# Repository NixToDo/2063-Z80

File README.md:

# Retro Z80 CPU Board

This project is a small changed copy of the great design from John Winans. I have added a J3A1 connector to get the IORQ_50, IORQ_60 and SIO_IEO from the PCB.

This project was designed to run CP/M 2.2 from an SD card.  It should be an attainable goal for anyone that can solder through-hole parts to assemble it. Note that J10 is an optional header that allows a Sparkfun SD card breakout board [DEV-13743](https://www.digikey.com/en/products/detail/sparkfun-electronics/DEV-13743/5881845) to used instead of soldering on the surface-mount SD socket part.

## Where to get Boards & Software

* You can order boards from any prototype PCB vendor.  For example, I show how you can order these boards from [JLCPCB](https://jlcpcb.com/) or [OSHPark](https://oshpark.com/) by uploading the gerber files found in the releases of this and the flash programmer projects as shown in this [Z80 Retro! - How To Order PC Boards](https://youtu.be/AUg_sbPnzn0) video on YouTube.
  - Gerber files for the CPU board: [2063-Z80-v3](https://github.com/johnwinans/2063-Z80/releases/download/v3/2063-Z80-gerbers.zip)
  - Gerber files for the FLASH programmer: [2065-Z80-programmer-v2](https://github.com/johnwinans/2065-Z80-programmer/releases/download/v2.0/2065-Z80-programmer-gerbers.zip) (This is used with a Raspberry PI to program the FLASH chip on the CPU board.)

* Software for this project can be found in my [2063-Z80-cpm](https://github.com/johnwinans/2063-Z80-cpm) repo.

* Note that the [FLASH programmer](https://github.com/johnwinans/2065-Z80-programmer) has been designed to work with a Raspberry PI in the event that you don't already own such programmer.  This companion programmer PCB should cost about $2 more when it is ordered at the same time as the CPU board from JLCPCB or other similar proto-board shops as shown in the [Z80 Retro! - How To Order PC Boards](https://youtu.be/AUg_sbPnzn0) video on YouTube.

## Links to Related Material

* A youtube playlist discussing this project and how to build your own can be found in [John's Basement](https://www.youtube.com/watch?v=oekucjDcNbA&list=PL3by7evD3F51Cf9QnsAEdgSQ4cz7HQZX5)
* A PDF version of the schematic can be found [here](2063-Z80.pdf).
* Here is the as-built [BOM](2063-Z80.md) with links to the datasheets for all the parts.
* Here is another [BOM](2063-Z80-sockets.md) with links to sockets for the chips.
* To configure a new PI for use with this programmer board as well as to develop Z80 code 
for the Z80 Retro board, see this [PI Setup Guide](https://github.com/johnwinans/raspberry-pi-install)
* More software for this project will be added as it evolves.

## Links to Related Datasheets Seen On YouTube

* [Z80 Datasheet PS0178](https://www.zilog.com/docs/z80/ps0178.pdf) with detailed timing diagrams.
* [Z80 User Manual UM0080](http://www.zilog.com/docs/z80/um0080.pdf) with detailed descriptions of each instruction.
* [Z80 CPU Peripherals User Manual UM0081](http://www.zilog.com/docs/z80/um0081.pdf) discusses the CTC and SIO.
* [Z80 Family Product Specifications Handbook - 1984](http://www.bitsavers.org/components/zilog/z80/Z80_Family_Product_Specifications_Handbook_Feb84.pdf) has nicer pictures of the SIO registers.
* [Wikipedia UART Article](https://en.wikipedia.org/wiki/Universal_asynchronous_receiver-transmitter)
* [AY-3-1015D UART Datasheet](https://rocelec.widen.net/view/pdf/bvesdj0cqf/GSIIS01845-1.pdf) (Has a discussion of the 16X bit-rate clock with diagrams etc. applicable to all UARTs.)

## Serial Port Cable Parts

* [How to make IDC cables](https://youtu.be/gZ420Z-8HuU) for the serial ports.
* [IDC 2x5 connectors](https://www.amazon.com/gp/product/B07S1NFG4S)
* [IDC D-SUB 9-pin connectors (Digikey)](https://www.digikey.com/en/products/detail/assmann-wsw-components/A-DSF-09LPIII-Z/924263)
* [IDC D-SUB 9-pin connectors (Amazon)](https://www.amazon.com/Uxcell-a15030600ux0494-Female-Connector-Ribbon/dp/B00YM41NTW)

## Parallel Port Cable Parts

* [IDC 2x13 connectors](https://www.amazon.com/gp/product/B07RXK96GV)
* [IDC D-SUB 25-pin connectors (Digikey)](https://www.digikey.com/en/products/detail/amphenol-icc-commercial-products/L17DBFRA25S/1972210)
* [IDC D-SUB 25-pin connectors (Amazon)](https://www.amazon.com/Fielect-Female-Adapter-Connector-Ribbon/dp/B082GMDNTS)

## Ribbon Cable

* [40-conductor (Amazon)](https://www.amazon.com/Eowpower-40Pin-40Way-Rainbow-Ribbon/dp/B079KQ6K3Y) - peel off a
 26-pin strip and a 10-pin strip to make one parallel and one serial cable (cut the 10-pin strip in half length-wise to make two serial cables.

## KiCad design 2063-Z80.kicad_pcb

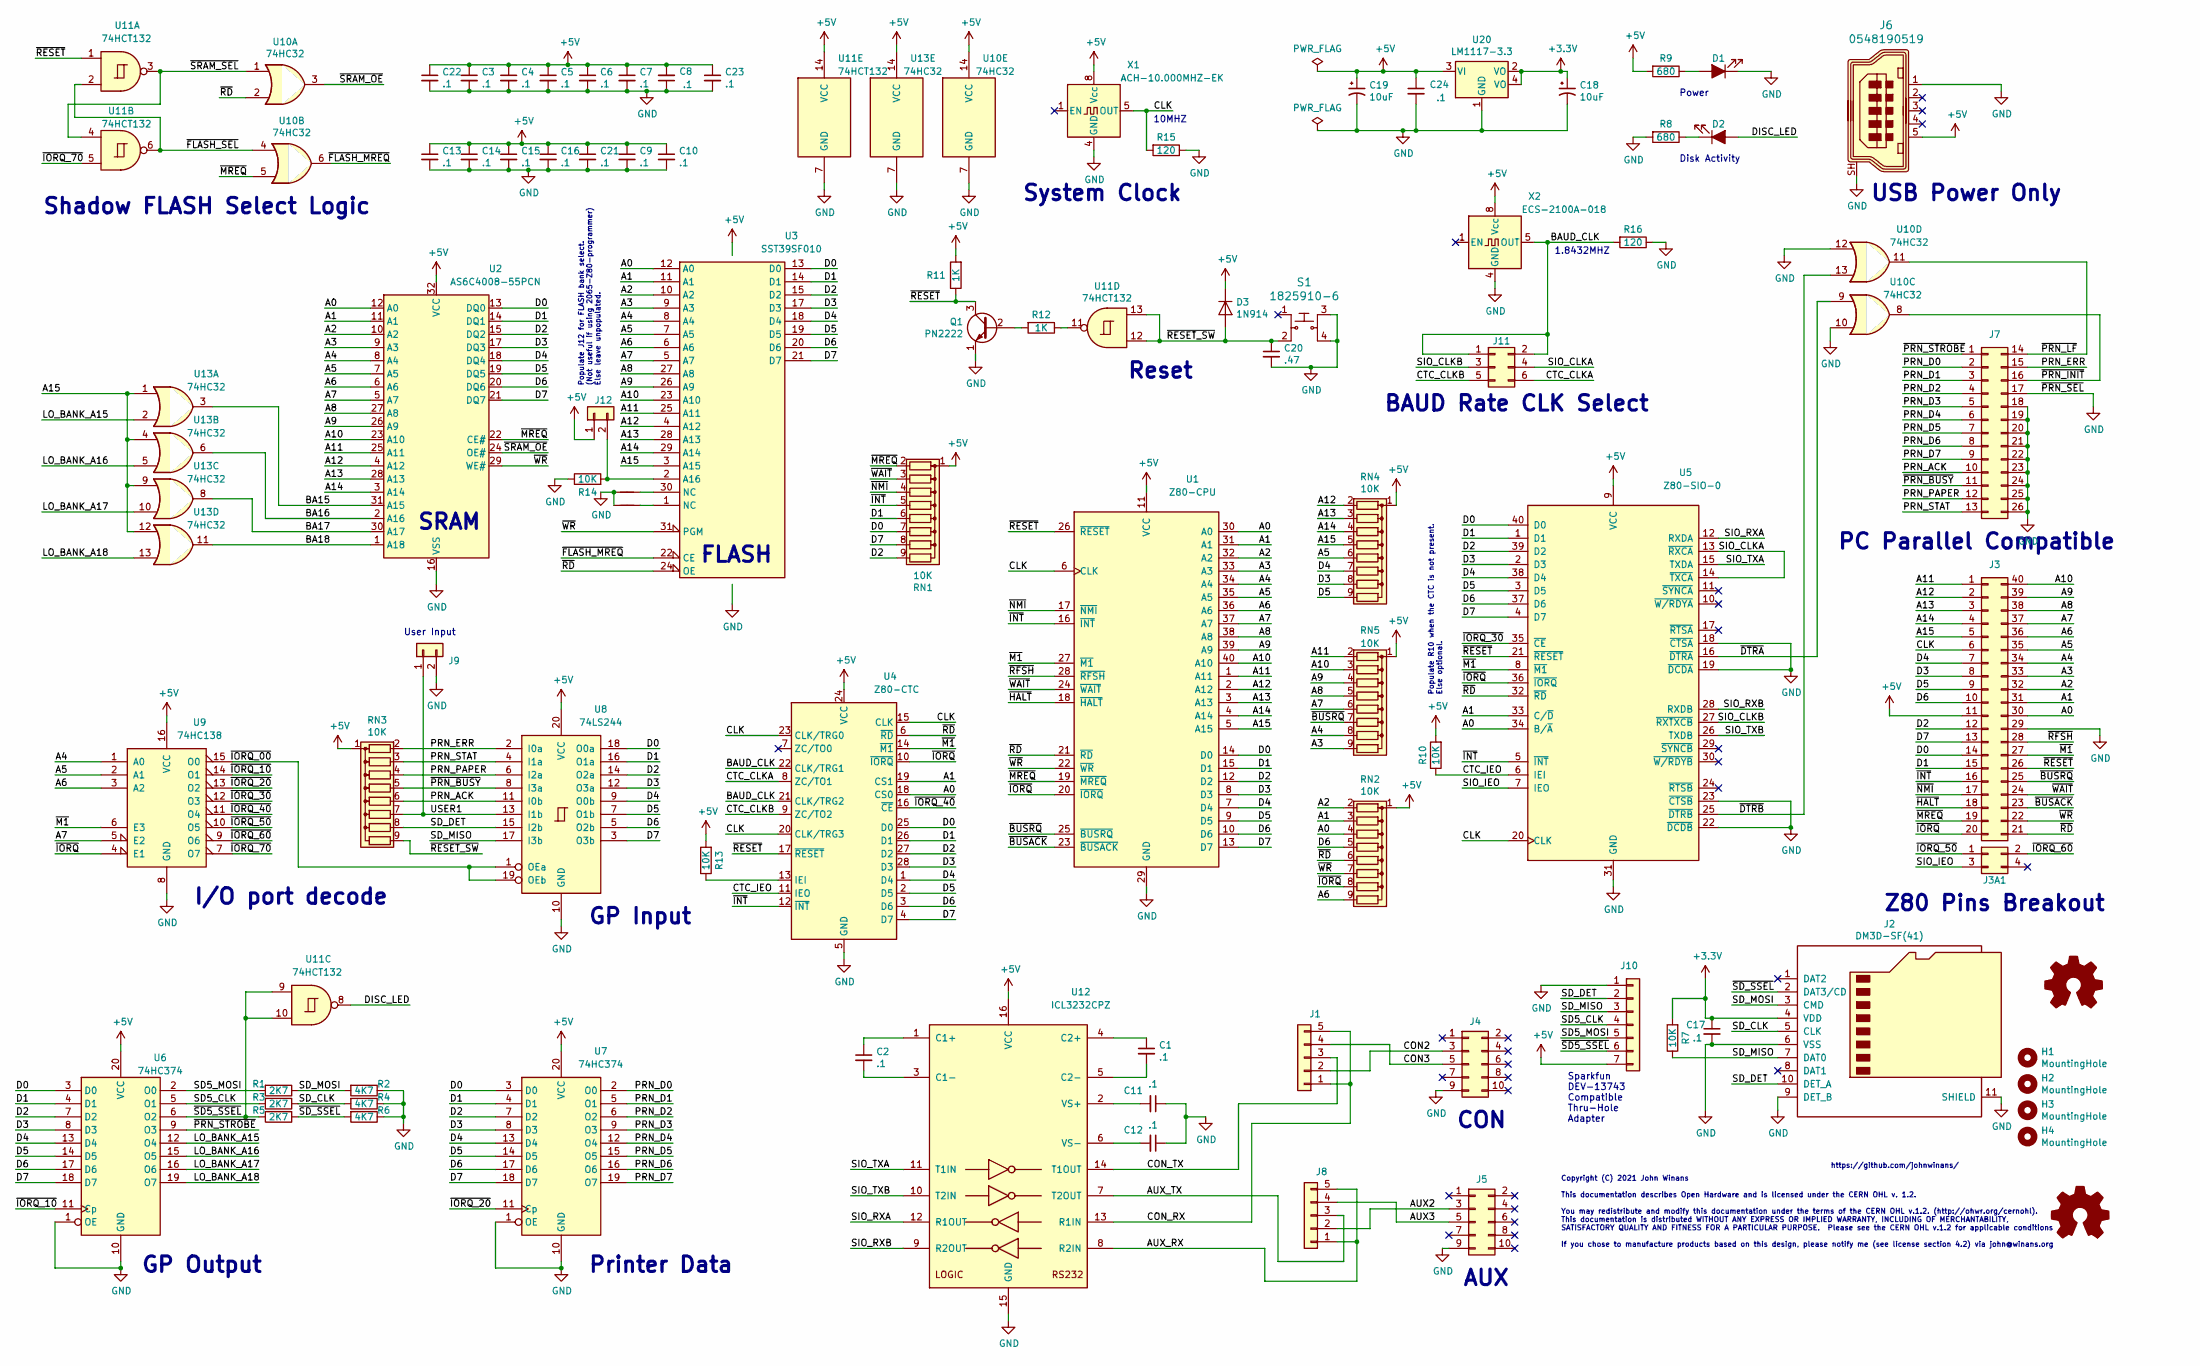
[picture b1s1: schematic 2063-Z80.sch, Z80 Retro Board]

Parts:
C1, C2, C3, C4, C5, C6, C7, C8, C9, C10, C11, C12, C13, C14, C15, C16, C21, C22, C23: .1; C_Disc_D3.0mm_W2.0mm_P2.50mm; MPN ‎C315C104M5U5TA7303‎; Digi-Key_PN 399-9859-1-ND
C17: .1; C_0805_2012Metric_Pad1.18x1.45mm_HandSolder; MPN CL10B104KB8NNWC; Digi-Key_PN 1276-1935-1-ND
C18: 10uF; C_0805_2012Metric_Pad1.18x1.45mm_HandSolder; MPN CL21A106MQFNNNE; Digi-Key_PN 1276-1298-1-ND
C19: 10uF; CP_Radial_D5.0mm_P2.50mm; MPN ECE-A1EKS100; Digi-Key_PN P975-ND
C20: .47; C_Disc_D3.0mm_W2.0mm_P2.50mm; MPN C315C474K5R5TA7303; Digi-Key_PN 399-14039-1-ND
C24: .1; C_0805_2012Metric_Pad1.15x1.40mm_HandSolder; MPN CL10B104KB8NNWC; Digi-Key_PN 1276-1935-1-ND
D1, D2: LED_ALT; LED_D3.0mm; MPN MV57640; Digi-Key_PN 1080-1122-ND
D3: 1N914; D_DO-35_SOD27_P7.62mm_Horizontal; MPN 1N4148TR; Digi-Key_PN 1N4148FSCT-ND
H1, H2, H3, H4: MountingHole; MountingHole_2.7mm
J1, J8: Conn_01x05; PinHeader_1x05_P2.54mm_Vertical; MPN PRPC005SFAN-RC; Digi-Key_PN S1211EC-05-ND
J2: DM3D-SF(41); microSD_HC_Hirose_DM3D-SF; MPN ‎DM3D-SF(41)‎; Digi-Key_PN H126097CT-ND (alternate: 114-00841-68-1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
J3: Conn_02x20; PinHeader_2x20_P2.54mm_Vertical_counterclock; MPN PRPC020DAAN-RC; Digi-Key_PN S2011EC-20-ND
J3A1: Conn_02x02_Odd_Even; PinHeader_2x02_P2.54mm_Vertical
J4, J5: Conn_02x05; PinHeader_2x05_P2.54mm_Vertical; MPN PR20205VBDN; Digi-Key_PN 1849-1002-ND
J6: 0548190519; USB_Mini_B_Female_548190519; MPN 0548190519; Digi-Key_PN A135698-ND
J7: Conn_02x13; PinHeader_2x13_P2.54mm_Top_Bottom; MPN PRPC013DAAN-RC; Digi-Key_PN S2011EC-13-ND
J9, J12: Conn_01x02; PinHeader_1x02_P2.54mm_Vertical; MPN PRPC002SAAN-RC; Digi-Key_PN S1011EC-02-ND
J10: Conn_01x07; PinHeader_1x07_P2.54mm_Vertical; MPN PRPC007SAAN-RC; Digi-Key_PN S1011EC-07-ND
J11: Conn_02x03; PinHeader_2x03_P2.54mm_Vertical; MPN PH2-06-UA; Digi-Key_PN 2057-PH2-06-UA-ND
LOGO1: OSHW_Logo; OSHW-Logo_11.4x12mm_SilkScreen
LOGO2: OSHW_Logo; OSHW-Logo_5.7x6mm_SilkScreen
NT1, NT2: Net-Tie_2; NetTie-2_SMD_Pad0.5mm
Q1: PN2222; TO-92L; MPN PN2222A PBFREE; Digi-Key_PN 1514-PN2222APBFREE-ND
R1, R3, R5: 2K7; R_Axial_DIN0204_L3.6mm_D1.6mm_P5.08mm_Horizontal; MPN ‎CF18JT2K70‎; Digi-Key_PN CF18JT2K70CT-ND
R2, R4, R6: 4K7; R_Axial_DIN0204_L3.6mm_D1.6mm_P5.08mm_Horizontal; MPN ‎CF18JT4K70‎; Digi-Key_PN CF18JT4K70CT-ND
R7, R10, R13, R14: 10K; R_Axial_DIN0204_L3.6mm_D1.6mm_P5.08mm_Horizontal; MPN CF18JT10K0; Digi-Key_PN CF18JT10K0CT-ND
R8, R9: 680; R_Axial_DIN0204_L3.6mm_D1.6mm_P5.08mm_Horizontal; MPN ‎CF18JT680R‎; Digi-Key_PN CF18JT680RCT-ND‎
R11, R12: 1K; R_Axial_DIN0204_L3.6mm_D1.6mm_P5.08mm_Horizontal; MPN ‎CF18JT1K00‎; Digi-Key_PN CF18JT1K00CT-ND‎
R15, R16: 120; R_Axial_DIN0204_L3.6mm_D1.6mm_P5.08mm_Horizontal; MPN CF18JT120R; Digi-Key_PN CF18JT120RCT-ND
RN1, RN2, RN3, RN4, RN5: 10K; R_Array_SIP9; MPN ‎4609X-101-103LF‎; Digi-Key_PN 4609X-101-103LF-ND‎
S1: 1825910-6; Switch_Tactile_THT_6x6mm; MPN 1825910-6; Digi-Key_PN 450-1650-ND
U1: Z80-CPU; DIP-40_W15.24mm_Socket; MPN Z84C0010PEG‎; Digi-Key_PN 269-3898-ND
U2: AS6C4008-55PCN; DIP-32_W15.24mm_Socket; MPN AS6C4008-55PIN; Digi-Key_PN 1450-1178-5-ND‎
U3: SST39SF010; DIP-32_W15.24mm_Socket; MPN SST39SF010A-70-4C-PHE; Digi-Key_PN SST39SF010A-70-4C-PHE-ND‎
U4: Z80-CTC; DIP-28_W15.24mm_Socket; MPN Z84C3010PEG‎; Digi-Key_PN 269-3914-ND
U5: Z80-SIO-0; DIP-40_W15.24mm_Socket; MPN Z84C4010PEG‎; Digi-Key_PN 269-5062-ND‎
U6, U7: 74HC374; DIP-20_W7.62mm_Socket; MPN CD74HC374E; Digi-Key_PN 296-12806-5-ND
U8: 74LS244; DIP-20_W7.62mm_Socket; MPN SN74LS244NE4; Digi-Key_PN 296-36148-5-ND
U9: 74HC138; DIP-16_W7.62mm_Socket; MPN SN74HC138AN; Digi-Key_PN 296-SN74HC138AN-ND
U10, U13: 74HC32; DIP-14_W7.62mm_Socket; MPN CD74HC32E; Digi-Key_PN 296-12803-5-ND
U11: 74HCT132; DIP-14_W7.62mm_Socket; MPN CD74HCT132E; Digi-Key_PN 296-2090-5-ND
U12: ICL3232CPZ; DIP-16_W7.62mm_Socket; MPN ‎ICL3232CPZ‎; Digi-Key_PN ICL3232CPZ-ND‎
U20: LM1117-3.3; SOT-223; MPN NCP1117ST33T3G; Digi-Key_PN NCP1117ST33T3GOSCT-ND
X1: ACH-10.000MHZ-EK; Oscillator_DIP-8_combo; MPN ACH-10.000MHZ-EK; Digi-Key_PN 535-9167-5-ND
X2: ECS-2100A-018; Oscillator_DIP-8_combo; MPN ‎ECS-2100A-018‎; Digi-Key_PN XC231-ND‎

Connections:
+3V3: C17.1, C18.1, J2.4 (VDD), R7.2, U20.2 (VO), U20.4 (VO)
+5V: C3.1, C4.1, C5.1, C6.1, C7.1, C8.2, C9.1, C10.1, C13.1, C14.1, C15.1, C16.1, C19.1, C21.1, C22.1, C23.1, C24.1, D3.1 (K), J3.11, J6.5, J10.7, J12.1, R9.2, R10.2, R11.2, R13.2, RN1.1 (common), RN2.1 (common), RN3.1 (common), RN4.1 (common), RN5.1 (common), U1.11 (VCC), U2.32 (VCC), U3.32 (VCC), U4.24 (VCC), U5.9 (VCC), U6.20 (VCC), U7.20 (VCC), U8.20 (VCC), U9.16 (VCC), U10.14 (VCC), U11.14 (VCC), U12.16 (VCC), U13.14 (VCC), U20.3 (VI), X1.8 (Vcc), X2.8 (Vcc)
/A0: J3.30, RN2.4 (R3), U1.30 (A0), U2.12 (A0), U3.12 (A0), U4.18 (CS0), U5.34 (B/~A)
/A1: J3.31, RN2.3 (R2), U1.31 (A1), U2.11 (A1), U3.11 (A1), U4.19 (CS1), U5.33 (C/~D)
/A2: J3.32, RN2.2 (R1), U1.32 (A2), U2.10 (A2), U3.10 (A2)
/A3: J3.33, RN5.9 (R8), U1.33 (A3), U2.9 (A3), U3.9 (A3)
/A4: J3.34, RN5.8 (R7), U1.34 (A4), U2.8 (A4), U3.8 (A4), U9.1 (A0)
/A5: J3.35, RN4.6 (R5), U1.35 (A5), U2.7 (A5), U3.7 (A5), U9.2 (A1)
/A6: J3.36, RN2.9 (R8), U1.36 (A6), U2.6 (A6), U3.6 (A6), U9.3 (A2)
/A7: J3.37, RN5.6 (R5), U1.37 (A7), U2.5 (A7), U3.5 (A7), U9.5 (E2)
/A8: J3.38, RN5.5 (R4), U1.38 (A8), U2.27 (A8), U3.27 (A8)
/A9: J3.39, RN5.4 (R3), U1.39 (A9), U2.26 (A9), U3.26 (A9)
/A10: J3.40, RN5.3 (R2), U1.40 (A10), U2.23 (A10), U3.23 (A10)
/A11: J3.1, RN5.2 (R1), U1.1 (A11), U2.25 (A11), U3.25 (A11)
/A12: J3.2, RN4.2 (R1), U1.2 (A12), U2.4 (A12), U3.4 (A12)
/A13: J3.3, RN4.3 (R2), U1.3 (A13), U2.28 (A13), U3.28 (A13)
/A14: J3.4, RN4.4 (R3), U1.4 (A14), U2.3 (A14), U3.29 (A14)
/A15: J3.5, RN4.5 (R4), U1.5 (A15), U3.3 (A15), U13.1, U13.4, U13.9, U13.12
/AUX2: J5.3, J8.2
/AUX3: J5.5, J8.4
/AUX_RX: J8.1, J8.5, U12.8 (R2IN)
/AUX_TX: J8.3, U12.7 (T2OUT)
/BA15: U2.31 (A15), U13.3
/BA16: U2.2 (A16), U13.6
/BA17: U2.30 (A17), U13.8
/BA18: U2.1 (A18), U13.11
/BAUD_CLK: J11.1, J11.2, R16.2, U4.21 (CLK/TRG2), U4.22 (CLK/TRG1), X2.5 (OUT)
/CLK: J3.6, R15.2, U1.6 (CLK), U4.15 (CLK), U4.20 (CLK/TRG3), U4.23 (CLK/TRG0), U5.20 (CLK), X1.5 (OUT)
/CON2: J1.2, J4.3
/CON3: J1.4, J4.5
/CON_RX: J1.1, J1.5, U12.13 (R1IN)
/CON_TX: J1.3, U12.14 (T1OUT)
/CTC_CLKA: J11.6, U4.8 (ZC/TO1)
/CTC_CLKB: J11.5, U4.9 (ZC/TO2)
/CTC_IEO: R10.1, U4.11 (IEO), U5.6 (IEI)
/D0: J3.14, RN1.7 (R6), U1.14 (D0), U2.13 (DQ0), U3.13 (D0), U4.25 (D0), U5.40 (D0), U6.3 (D0), U7.3 (D0), U8.18 (O0a)
/D1: J3.15, RN1.6 (R5), U1.15 (D1), U2.14 (DQ1), U3.14 (D1), U4.26 (D1), U5.1 (D1), U6.4 (D1), U7.4 (D1), U8.16 (O1a)
/D2: J3.12, RN1.9 (R8), U1.12 (D2), U2.15 (DQ2), U3.15 (D2), U4.27 (D2), U5.39 (D2), U6.7 (D2), U7.7 (D2), U8.14 (O2a)
/D3: J3.8, RN4.8 (R7), U1.8 (D3), U2.17 (DQ3), U3.17 (D3), U4.28 (D3), U5.2 (D3), U6.8 (D3), U7.8 (D3), U8.12 (O3a)
/D4: J3.7, RN4.7 (R6), U1.7 (D4), U2.18 (DQ4), U3.18 (D4), U4.1 (D4), U5.38 (D4), U6.13 (D4), U7.13 (D4), U8.9 (O0b)
/D5: J3.9, RN4.9 (R8), U1.9 (D5), U2.19 (DQ5), U3.19 (D5), U4.2 (D5), U5.3 (D5), U6.14 (D5), U7.14 (D5), U8.7 (O1b)
/D6: J3.10, RN2.5 (R4), U1.10 (D6), U2.20 (DQ6), U3.20 (D6), U4.3 (D6), U5.37 (D6), U6.17 (D6), U7.17 (D6), U8.5 (O2b)
/D7: J3.13, RN1.8 (R7), U1.13 (D7), U2.21 (DQ7), U3.21 (D7), U4.4 (D7), U5.4 (D7), U6.18 (D7), U7.18 (D7), U8.3 (O3b)
/DISC_LED: D2.2 (A), U11.8
/LO_BANK_A15: U6.12 (O4), U13.2
/LO_BANK_A16: U6.15 (O5), U13.5
/LO_BANK_A17: U6.16 (O6), U13.10
/LO_BANK_A18: U6.19 (O7), U13.13
/PRN_ACK: J7.10, RN3.6 (R5), U8.11 (I0b)
/PRN_D0: J7.2, U7.2 (O0)
/PRN_D1: J7.3, U7.5 (O1)
/PRN_D2: J7.4, U7.6 (O2)
/PRN_D3: J7.5, U7.9 (O3)
/PRN_D4: J7.6, U7.12 (O4)
/PRN_D5: J7.7, U7.15 (O5)
/PRN_D6: J7.8, U7.16 (O6)
/PRN_D7: J7.9, U7.19 (O7)
/PRN_ERR: J7.15, RN3.2 (R1), U8.2 (I0a)
/PRN_PAPER: J7.12, RN3.4 (R3), U8.6 (I2a)
/PRN_STAT: J7.13, RN3.3 (R2), U8.4 (I1a)
/SD5_CLK: J10.4, R3.2, U6.5 (O1)
/SD5_MOSI: J10.5, R1.2, U6.2 (O0)
/SD_CLK: J2.5 (CLK), R3.1, R4.2
/SD_DET: J2.10 (DET_A), J10.2, RN3.8 (R7), U8.15 (I2b)
/SD_MISO: J2.7 (DAT0), J10.3, R7.1, U8.17 (I3b)
/SD_MOSI: J2.3 (CMD), R1.1, R2.2
/SIO_CLKA: J11.4, U5.13 (~RXCA), U5.14 (~TXCA)
/SIO_CLKB: J11.3, U5.27 (~RXTXCB)
/SIO_IEO: J3A1.3, U5.7 (IEO)
/SIO_RXA: U5.12 (RXDA), U12.12 (R1OUT)
/SIO_RXB: U5.28 (RXDB), U12.9 (R2OUT)
/SIO_TXA: U5.15 (TXDA), U12.11 (T1IN)
/SIO_TXB: U5.26 (TXDB), U12.10 (T2IN)
/USER1: J9.1, RN3.7 (R6), U8.13 (I1b)
/~BUSACK: J3.23, U1.23 (~BUSACK~)
/~BUSRQ: J3.25, RN5.7 (R6), U1.25 (~BUSRQ~)
/~DTRA: U5.16 (~DTRA), U10.9
/~DTRB: U5.25 (~DTRB), U10.13
/~FLASH_MREQ: U3.22 (CE), U10.6
/~FLASH_SEL: U10.4, U11.2, U11.6
/~HALT: J3.18, U1.18 (~HALT~)
/~INT: J3.16, RN1.5 (R4), U1.16 (~INT~), U4.12 (~INT), U5.5 (~INT)
/~IORQ: J3.20, RN2.8 (R7), U1.20 (~IORQ~), U4.10 (~IORQ), U5.36 (~IORQ), U9.4 (E1)
/~IORQ_00: U8.1 (OEa), U8.19 (OEb), U9.15 (O0)
/~IORQ_10: U6.11 (Cp), U9.14 (O1)
/~IORQ_20: U7.11 (Cp), U9.13 (O2)
/~IORQ_30: U5.35 (~CE), U9.12 (O3)
/~IORQ_40: U4.16 (~CE), U9.11 (O4)
/~IORQ_50: J3A1.1, U9.10 (O5)
/~IORQ_60: J3A1.2, U9.9 (O6)
/~IORQ_70: U9.7 (O7), U11.5
/~M1: J3.27, U1.27 (~M1~), U4.14 (~M1), U5.8 (~M1), U9.6 (E3)
/~MREQ: J3.19, RN1.2 (R1), U1.19 (~MREQ~), U2.22 (CE#), U10.5
/~NMI: J3.17, RN1.4 (R3), U1.17 (~NMI~)
/~PRN_BUSY: J7.11, RN3.5 (R4), U8.8 (I3a)
/~PRN_INIT: J7.16, U10.8
/~PRN_LF: J7.14, U10.11
/~PRN_STROBE: J7.1, U6.9 (O3)
/~RD: J3.21, RN2.6 (R5), U1.21 (~RD~), U3.24 (OE), U4.6 (~RD), U5.32 (~RD), U10.2
/~RESET: J3.26, Q1.3 (C), R11.1, U1.26 (~RESET~), U4.17 (~RESET), U5.21 (~RESET), U11.1
/~RESET_SW: C20.1, D3.2 (A), RN3.9 (R8), S1.2, U11.12, U11.13
/~RFSH: J3.28, U1.28 (~RFSH~)
/~SD5_SSEL: J10.6, R5.2, U6.6 (O2), U11.9, U11.10
/~SD_SSEL: J2.2 (DAT3/CD), R5.1, R6.2
/~SRAM_OE: U2.24 (OE#), U10.3
/~SRAM_SEL: U10.1, U11.3, U11.4
/~WAIT: J3.24, RN1.3 (R2), U1.24 (~WAIT~)
/~WR: J3.22, RN2.7 (R6), U1.22 (~WR~), U2.29 (WE#), U3.31 (PGM)
GND: C3.2, C4.2, C5.2, C6.2, C7.2, C8.1, C9.2, C10.2, C11.1, C12.1, C13.2, C14.2, C15.2, C16.2, C17.2, C18.2, C19.2, C20.2, C21.2, C22.2, C23.2, C24.2, D1.1 (K), J2.6 (VSS), J2.9 (DET_B), J2.11 (SHIELD), J3.29, J4.9, J5.9, J6.1, J6.SH, J7.17, J7.18, J7.19, J7.20, J7.21, J7.22, J7.23, J7.24, J7.25, J7.26, J9.2, J10.1, NT1.1, NT2.1, Q1.1 (E), R2.1, R4.1, R6.1, R8.2, R14.1, R15.1, R16.1, S1.3, S1.4, U1.29 (GND), U2.16 (VSS), U3.16 (GND), U4.5 (GND), U5.18 (~CTSA), U5.19 (~DCDA), U5.22 (~DCDB), U5.23 (~CTSB), U5.31 (GND), U6.1 (OE), U6.10 (GND), U7.1 (OE), U7.10 (GND), U8.10 (GND), U9.8 (GND), U10.7 (GND), U10.10, U10.12, U11.7 (GND), U12.15 (GND), U13.7 (GND), U20.1 (GND), X1.4 (GND), X2.4 (GND)
unnamed: C1.1, U12.4 (C2+)
unnamed: C1.2, U12.5 (C2-)
unnamed: C2.1, U12.1 (C1+)
unnamed: C2.2, U12.3 (C1-)
unnamed: C11.2, U12.2 (VS+)
unnamed: C12.2, U12.6 (VS-)
unnamed: D1.2 (A), R9.1
unnamed: D2.1 (K), R8.1
unnamed: J12.2, R14.2, U3.2 (A16)
unnamed: NT1.2, U3.30 (NC)
unnamed: NT2.2, U3.1 (NC)
unnamed: Q1.2 (B), R12.2
unnamed: R12.1, U11.11
unnamed: R13.1, U4.13 (IEI)

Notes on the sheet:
Disk Activity
Power
USB Power Only
Z80 Pins Breakout
Shadow FLASH Select Logic
FLASH
SRAM
GP Input
GP Output
Printer Data
PC Parallel Compatible
1.8432MHZ
I/O port decode
CON
AUX
Copyright (C) 2021 John Winans This documentation describes Open Hardware and is licensed under the CERN OHL v. 1.2. You may redistribute and modify this documentation under the terms of the CERN OHL v.1.2. (http://ohwr.org/cernohl). This documentation is distributed WITHOUT ANY EXPRESS OR IMPLIED 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
Reset
10MHZ
https://github.com/johnwinans/
Sparkfun DEV-13743 Compatible Thru-Hole Adapter
BAUD Rate CLK Select
System Clock
Populate R10 when the CTC is not present. Else optional.
User Input
Populate J12 for FLASH bank select. (Not useful if using 2065-Z80-programmer) Else leave unpopulated.

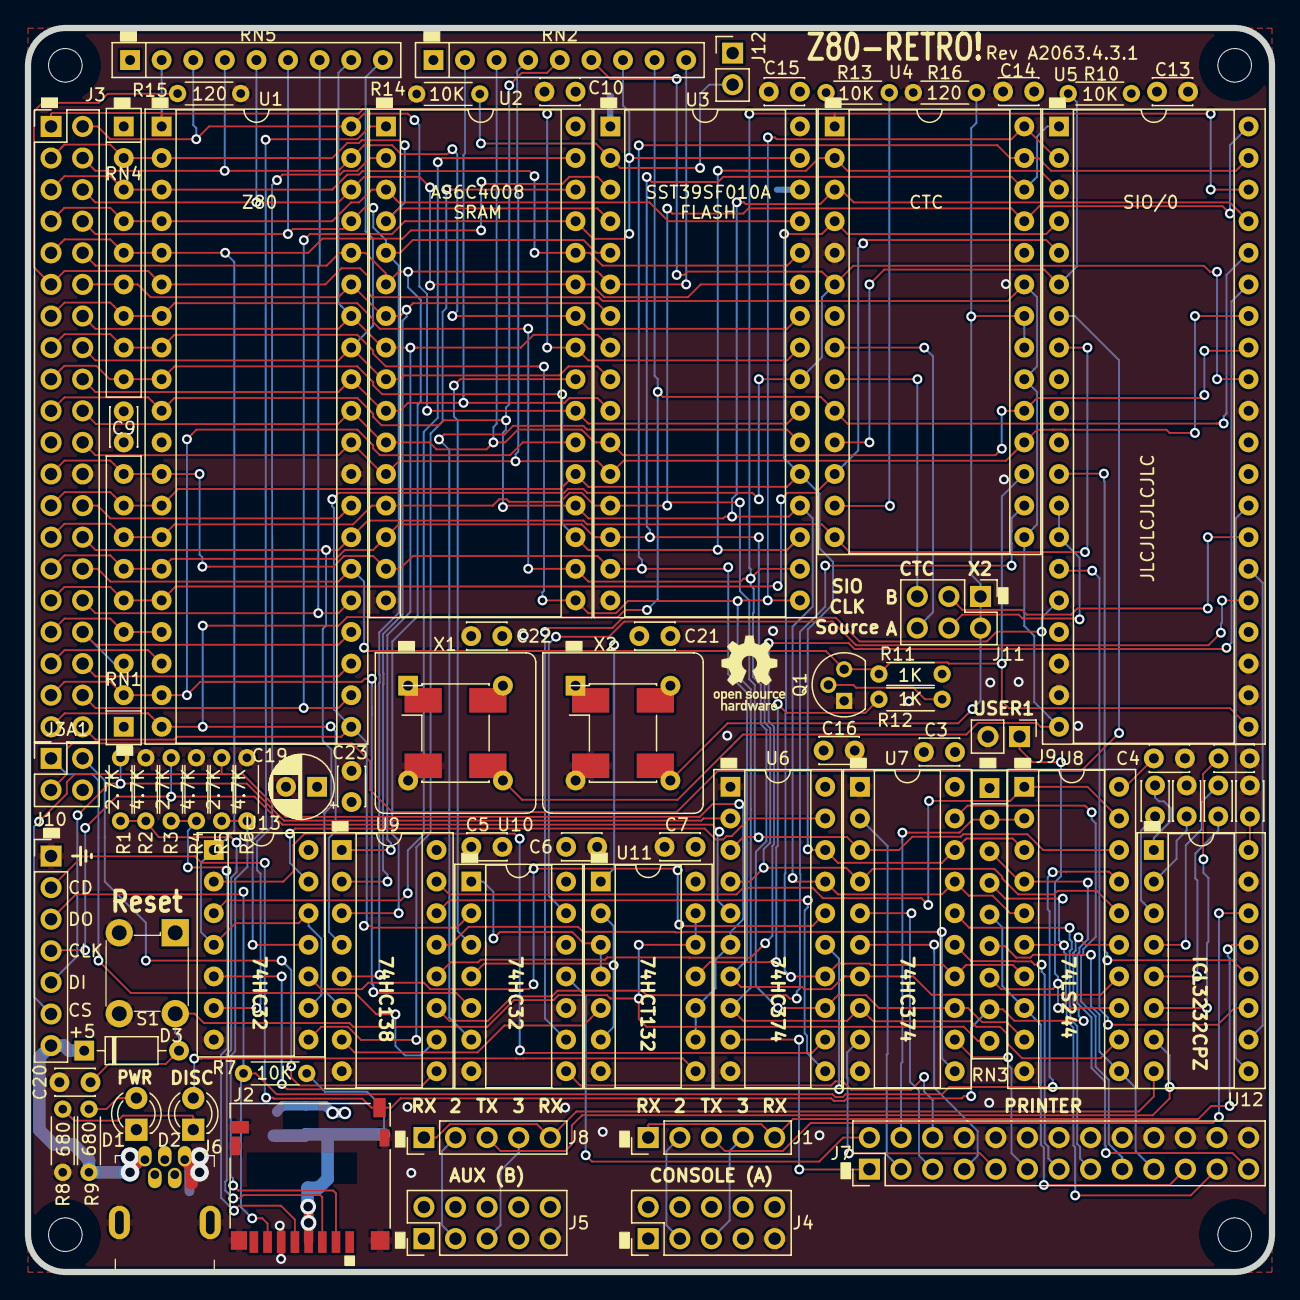
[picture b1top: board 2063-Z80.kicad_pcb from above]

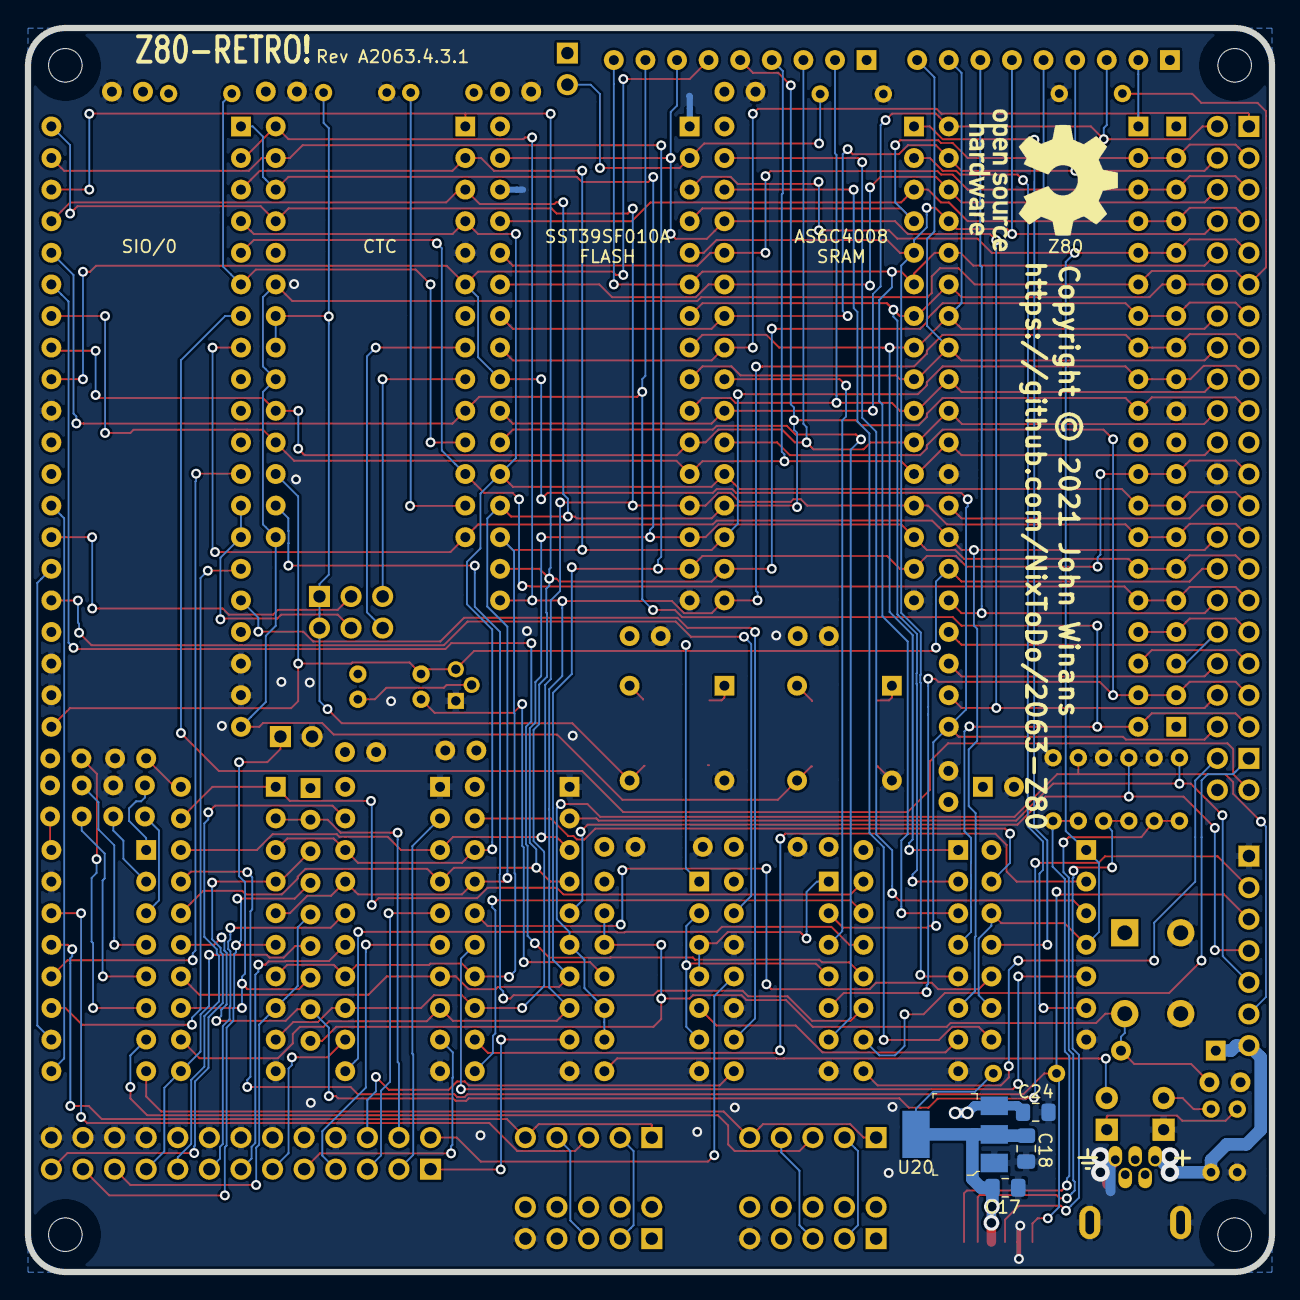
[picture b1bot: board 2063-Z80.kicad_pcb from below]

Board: 4 copper layers, 100.0 x 100.0 mm, 87 parts (7 on the bottom side), 123 nets.

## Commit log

2022-11-23 Added / Changed my PCB changes.
2022-11-23 Readme updated.
2022-12-18 Modified to fit my needs.

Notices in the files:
2063-Z80.kicad_pcb:
Copyright © 2021 John Winans
2063-Z80.sch:
If you chose to manufacture products based on this design, please notify me (see license section 4.2) via john@winans.org
